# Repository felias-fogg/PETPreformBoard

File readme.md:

# The PET Preform Board

The **PET Preform Board** board is a small PCB (67.8 x 15.6 mm) intended to be placed into a preform tube (with length of > 13cm) together with a 3.6 volt Lithium battery. On the board, you can place an ATtiny1634 and a dot matrix 5x7 display as well as some sensor breakout board (such as the popular GY boards). Meanwhile we have reached version *V4a* of the board design. In order to give an idea, here is a photo of this board in a preform tube.

With a barometer, you can, for example, ask people to take the tube and carry it up to the summit of a hill. At the summit, the display then reavals a code. An example for this usage is the [geocache at Dagstuhl castle](https://coord.info/GC4XBM2).

You'll find the Eagle files in the subdirectory *doc/eagle* together with pictures of how the PCB looks like. Let us now have a look at the top side.

On the right side, there is an ICSP header that one can use for programmig. Close to the ICSP header on the top, there is a 2-pin header for a power jumper. Without the jumper, the battery is cut off from the board. Then comes left of the ICSP header the place for the dot matrix display **DS1**, e.g., ***TA07-11SEKWA***. It is adivsable to chose a hyper-orange or hyper-red type because we can spare only a few mill Amps to light the dots. Even further left is the space for **IC1**, the MCU ***ATtiny1634***. Both the dot matrix display and the MCU have their respective 1-pins at the bottom to the left, as marked with the "1".

Left of the MCU, there is space for the *optional* resistor **R10** of 0Ω. Put that in if you want to connect the Vcc pin of a sensor directly to the battery. If you want to switch the power to the sensor, put instead the *optinonal* P-channel MOS-FET ***IRLML2244*** at the place marked Q1. 

Let us now look at the bottom of the board.

Now we start from the left, where we see the bottom of the ICSP header. Then there are SMD pads for an *optional* ***SQ-MIN-200*** or ***SQ-SEN-200*** vibration sensor. These are extremely sensitive, but also a bit expensive. Directly right to the pads are two through-hole pads that can be used for an alternative ***SW-18010*** vibration sensor, which is less expensive but also less sensitive.

The resistor **R7** is the pull-up for the vibration switch. The SW-18010 is usually open, but the SQ-xxx-200 switch is usually closed. So, 3MΩ seems to be a good value, limiting the quiescent current to roughly 1.2 µA. Currently, I use 10MΩ, which still works fine and saves even more power. The resistors **R2**-**R6** are current limiting resistors for the dot matrix display columns. I have labled them with 470Ω, but you also can use 330Ω or a lower value. You get a brighter display, but consume more power.  **R1** (10kΩ) is the usual pullup for the reset line and **C1** (100nF) is the blocking capacitor for the MCU. 

**R9** (10kΩ) is the pull-up for the MOSFET gate and **R8** (150Ω) is the current limiting resistor for the MOSFET. These two are, of course only necessary if one uses the MOSFET.

If you want to drive the sensor directly from the MCU pin, then **R8** should be 0Ω and you need to put another such bridge from the gate pad to the drain pad of the MOSFET.

Out of the 17 I/O lines of the ATtiny1634, 12 are used for the dot matrix display, one line is used for the vibration switch, two lines are dedicated for I2C, but could be used for other pusposes, one line is intended to be used for switching the MOSFET, and one line can be used as a TX line for debug outputs or it can be used for any other purpose. The pin assignment is described in the following table.

| MCU pin | MCU function | Arduino pin | Function | Display pin |
| -------:| :------------| -----------:|:---------| -------:|
| 1       |TX0/PB0/ADC5  |        A5/0 | TX/GPIO  |         |
| 2       |RX0/PA7/PCINT7|        A4/1 | Vib/GPIO |         |
| 3       | PA6          |           2 | Row 7    | 6       |
| 4       | PA5          |           3 | Row 6    | 5       | 
| 5       | PA4          |           4 | Row 5    | 4       |
| 6       | PA3          |           5 | Row 3    | 2       |
| 7       | PA2          |           6 | Column 2 | 3       |
| 8       | PA1          |           7 |Power/GPIO|         |
| 9       | PA0          |           8 | Column 1 | 1       |
| 10      | GND          |             | GND      |         |
| 11      | Vcc          |             | Vcc      |         |
| 12      | PC5          |           9 | Column 5 | 8       |
| 13      | PC4          |          10 | Column 4 | 7       |
| 14      | RESET        |             |          |         |
| 15      | PC2          |          11 | Row 1    | 12      |
| 16      | PC1/SCK/SCL  |       A10/12| ICSP/I2C/GPIO |    |
| 17      | PC0          |          13 | Row 2    | 11      |
| 18      | PB3          |          14 | Row 4    | 9       |
| 19      | PB2/MISO     |          15 | ICSP/Column 3 | 10 |
| 20      | PB1/MOSI/SDA |       A6/16 | ICSP/I2C/GPIO |    |

An include file for the current version of the board is **PETPreformBoard.h** in the *src* direct

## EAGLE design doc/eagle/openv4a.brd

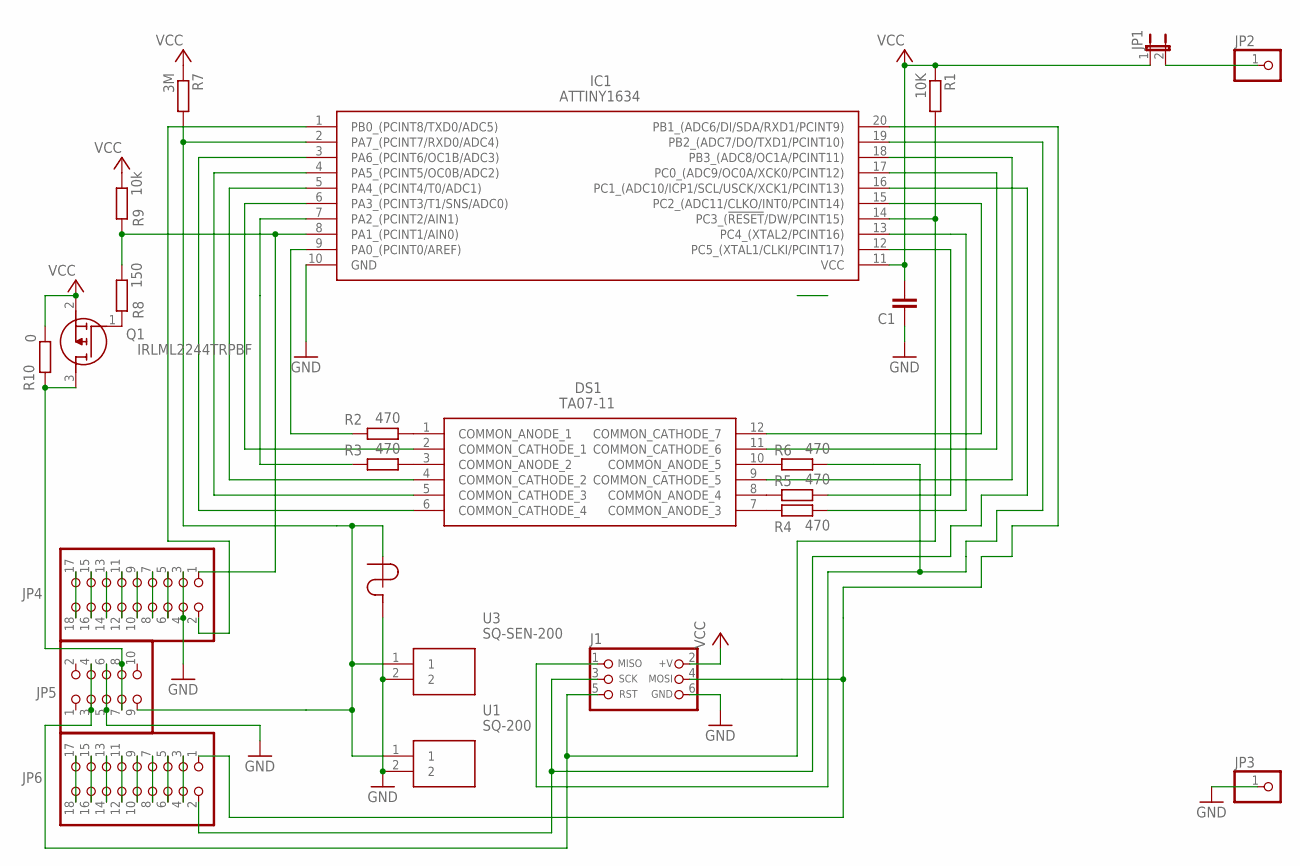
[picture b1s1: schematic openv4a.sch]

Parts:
C1: 100nF; C0805
DS1: TA07-11; DIPS762W75P254L1778H665Q12N; MANUFACTURER_PART_NUMBER TA07-11
IC1: ATTINY1634; SOIC127P1032X265-20N
J1: CON_HEADER_PRG_AVR_ICSP-PTH; HEADER_PRG_2X03
JP1: JP1E; JP1
JP2, JP3: PINHD-1X1; 1X01
JP4, JP6: PINHD-2X9; 2X09
JP5: PINHD-2X5; 2X05
Q1: IRLML2244TRPBF; SOT95P237X112-3N
R1: 10K; R0805
R2, R3, R4, R5, R6: 470; R0805
R7: 3M; R0805
R8: 150; R0805
R9: 10k; R0805
R10: 0; R0805
U1: SQ-200; SQMIN200
U2: VIB-SENS; SW-18010P
U3: SQ-SEN-200; SQSEN200

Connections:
GND: C1.1, IC1.10 (GND), J1.6 (GND), JP3.1, JP4.3, JP4.4, JP5.5, JP5.6, U1.2, U2.1, U3.2
unnamed: IC1.1 (PB0_(PCINT8/TXD0/ADC5)), JP4.2
unnamed: JP1.2, JP2.1
unnamed: DS1.1 (COMMON_ANODE_1), R2.2
unnamed: DS1.3 (COMMON_ANODE_2), R3.2
unnamed: DS1.7 (COMMON_ANODE_3), R4.1
unnamed: DS1.8 (COMMON_ANODE_4), R5.1
unnamed: DS1.10 (COMMON_ANODE_5), R6.1
unnamed: IC1.9 (PA0_(PCINT0/AREF)), R2.1
unnamed: IC1.8 (PA1_(PCINT1/AIN0)), JP4.1, R8.2, R9.1
unnamed: IC1.7 (PA2_(PCINT2/AIN1)), R3.1
unnamed: IC1.12 (PC5_(XTAL1/CLKI/PCINT17)), R5.2
unnamed: IC1.13 (PC4_(XTAL2/PCINT16)), R4.2
unnamed: DS1.2 (COMMON_CATHODE_1), IC1.6 (PA3_(PCINT3/T1/SNS/ADC0))
unnamed: DS1.4 (COMMON_CATHODE_2), IC1.5 (PA4_(PCINT4/T0/ADC1))
unnamed: DS1.5 (COMMON_CATHODE_3), IC1.4 (PA5_(PCINT5/OC0B/ADC2))
unnamed: DS1.6 (COMMON_CATHODE_4), IC1.3 (PA6_(PCINT6/OC1B/ADC3))
unnamed: IC1.19 (PB2_(ADC7/DO/TXD1/PCINT10)), J1.1 (MISO), R6.2
unnamed: JP4.5, JP4.6
unnamed: JP4.7, JP4.8
unnamed: JP4.9, JP4.10
unnamed: JP4.11, JP4.12
unnamed: JP4.13, JP4.14
unnamed: JP4.15, JP4.16
unnamed: JP4.17, JP4.18
unnamed: JP6.3, JP6.4
unnamed: JP6.5, JP6.6
unnamed: JP6.7, JP6.8
unnamed: JP6.9, JP6.10
unnamed: JP6.11, JP6.12
unnamed: JP6.13, JP6.14
unnamed: JP6.15, JP6.16
unnamed: JP6.17, JP6.18
unnamed: DS1.12 (COMMON_CATHODE_7), IC1.15 (PC2_(ADC11/CLKO/INT0/PCINT14))
unnamed: DS1.11 (COMMON_CATHODE_6), IC1.17 (PC0_(ADC9/OC0A/XCK0/PCINT12))
unnamed: IC1.16 (PC1_(ADC10/ICP1/SCL/USCK/XCK1/PCINT13)), J1.3 (SCK), JP6.2
unnamed: Q1.1 (G), R8.1
unnamed: IC1.20 (PB1_(ADC6/DI/SDA/RXD1/PCINT9)), J1.4 (MOSI), JP6.1
unnamed: DS1.9 (COMMON_CATHODE_5), IC1.18 (PB3_(ADC8/OC1A/PCINT11))
unnamed: IC1.2 (PA7_(PCINT7/RXD0/ADC4)), JP5.9, R7.2, U1.1, U2.2, U3.1
unnamed: IC1.14 (PC3_(!RESET!/DW/PCINT15)), J1.5 (RST), JP5.3, JP5.4, R1.2
unnamed: JP5.7, JP5.8, Q1.3 (D), R10.2
VCC: C1.2, IC1.11 (VCC), J1.2 (+V), JP1.1, Q1.2 (S), R1.1, R7.1, R9.2, R10.1

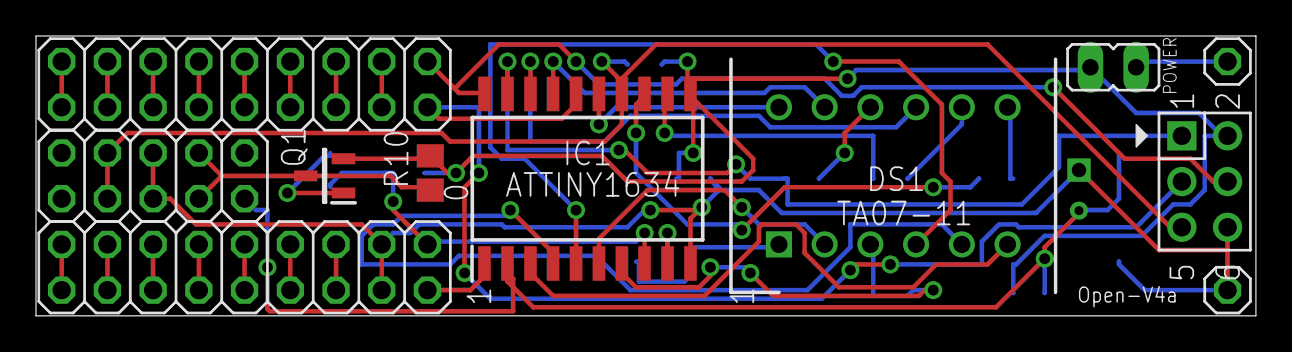
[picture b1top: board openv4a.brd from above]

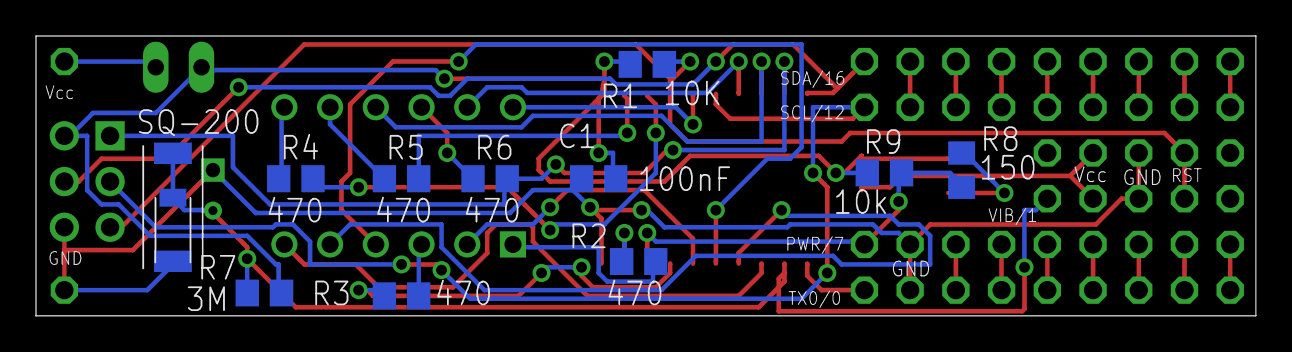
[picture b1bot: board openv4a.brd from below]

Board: 2 copper layers, 67.8 x 15.5 mm, 24 parts (13 on the bottom side), 43 nets.

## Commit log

2021-02-03 First public release
2021-02-03 V4.0.2 - typos corrected
2021-02-05 V4.0.3
2021-07-18 New Pic + video
2021-07-18 new readme
2023-11-13 fixed typos and added schematic
2023-11-13 bump version counter
2023-11-13 added schematic
2026-03-25 default is now 1634 and new movie
2026-03-25 new video
